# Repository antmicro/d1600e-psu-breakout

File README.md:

# Antmicro's open source D1600E PSU Breakout Board

Copyright (c) 2022-2023 [Antmicro](https://www.antmicro.com)

## Overview

This project contains open hardware design files for a Power Supply Unit (PSU) breakout board compatible with [Dell D1600E-S0 PSU](https://www.dell.com/en-us/work/shop/dell-power-supply-ac-1600-watt-psu-io/apd/450-ahuc/computer-chassis-components). 
The design files were prepared in KiCad.

### Project structure:

The main directory contains the KiCad design files, LICENSE and README.
The remaining files are stored in the following directories:

* ``img`` - contains graphics for this README
* ``doc`` - contains generated schematics and other documentation
* ``assets`` - contains visual assets for showcasing this design on [Open Hardware Portal](https://openhardware.antmicro.com/boards/d1600e-psu-breakout) and [Antmicro Designer](https://designer.antmicro.com/hardware/devices/d1600e-psu-breakout).

## Key features

* 5x power output channels providing 12V over 8-pin PCI Express type (Molex/39288080) sockets
* Up to 220W per single 12V power output channel
* Output current measurement implemented with [Ti/TMCS1100A2QDRQ1](https://www.ti.com/lit/ds/symlink/tmcs1100-q1.pdf) Hall sensors and 12-bit [Ti/ADS7828E](https://www.ti.com/lit/ds/symlink/ads7828.pdf) ADC accessible over I2C
* Power-cycling for each channel implemented with power MOSFETS driven from [Ti/TCA9534](https://www.ti.com/lit/ds/symlink/tca9534.pdf) GPIO expander accessible over I2C 
* I2C bus for current measurements and power cycling is opto-coupled with [FTDI/FT4232H-56Q](https://www.ftdichip.com/Support/Documents/DataSheets/ICs/DS_FT4232H.pdf) with USB exposed towards an external host
* Auxilary connector (Molex/39281103) exposing 5.0V,3.3V,12V for connecting external peripherals

## License

This project is published under the [Apache-2.0](LICENSE) license.

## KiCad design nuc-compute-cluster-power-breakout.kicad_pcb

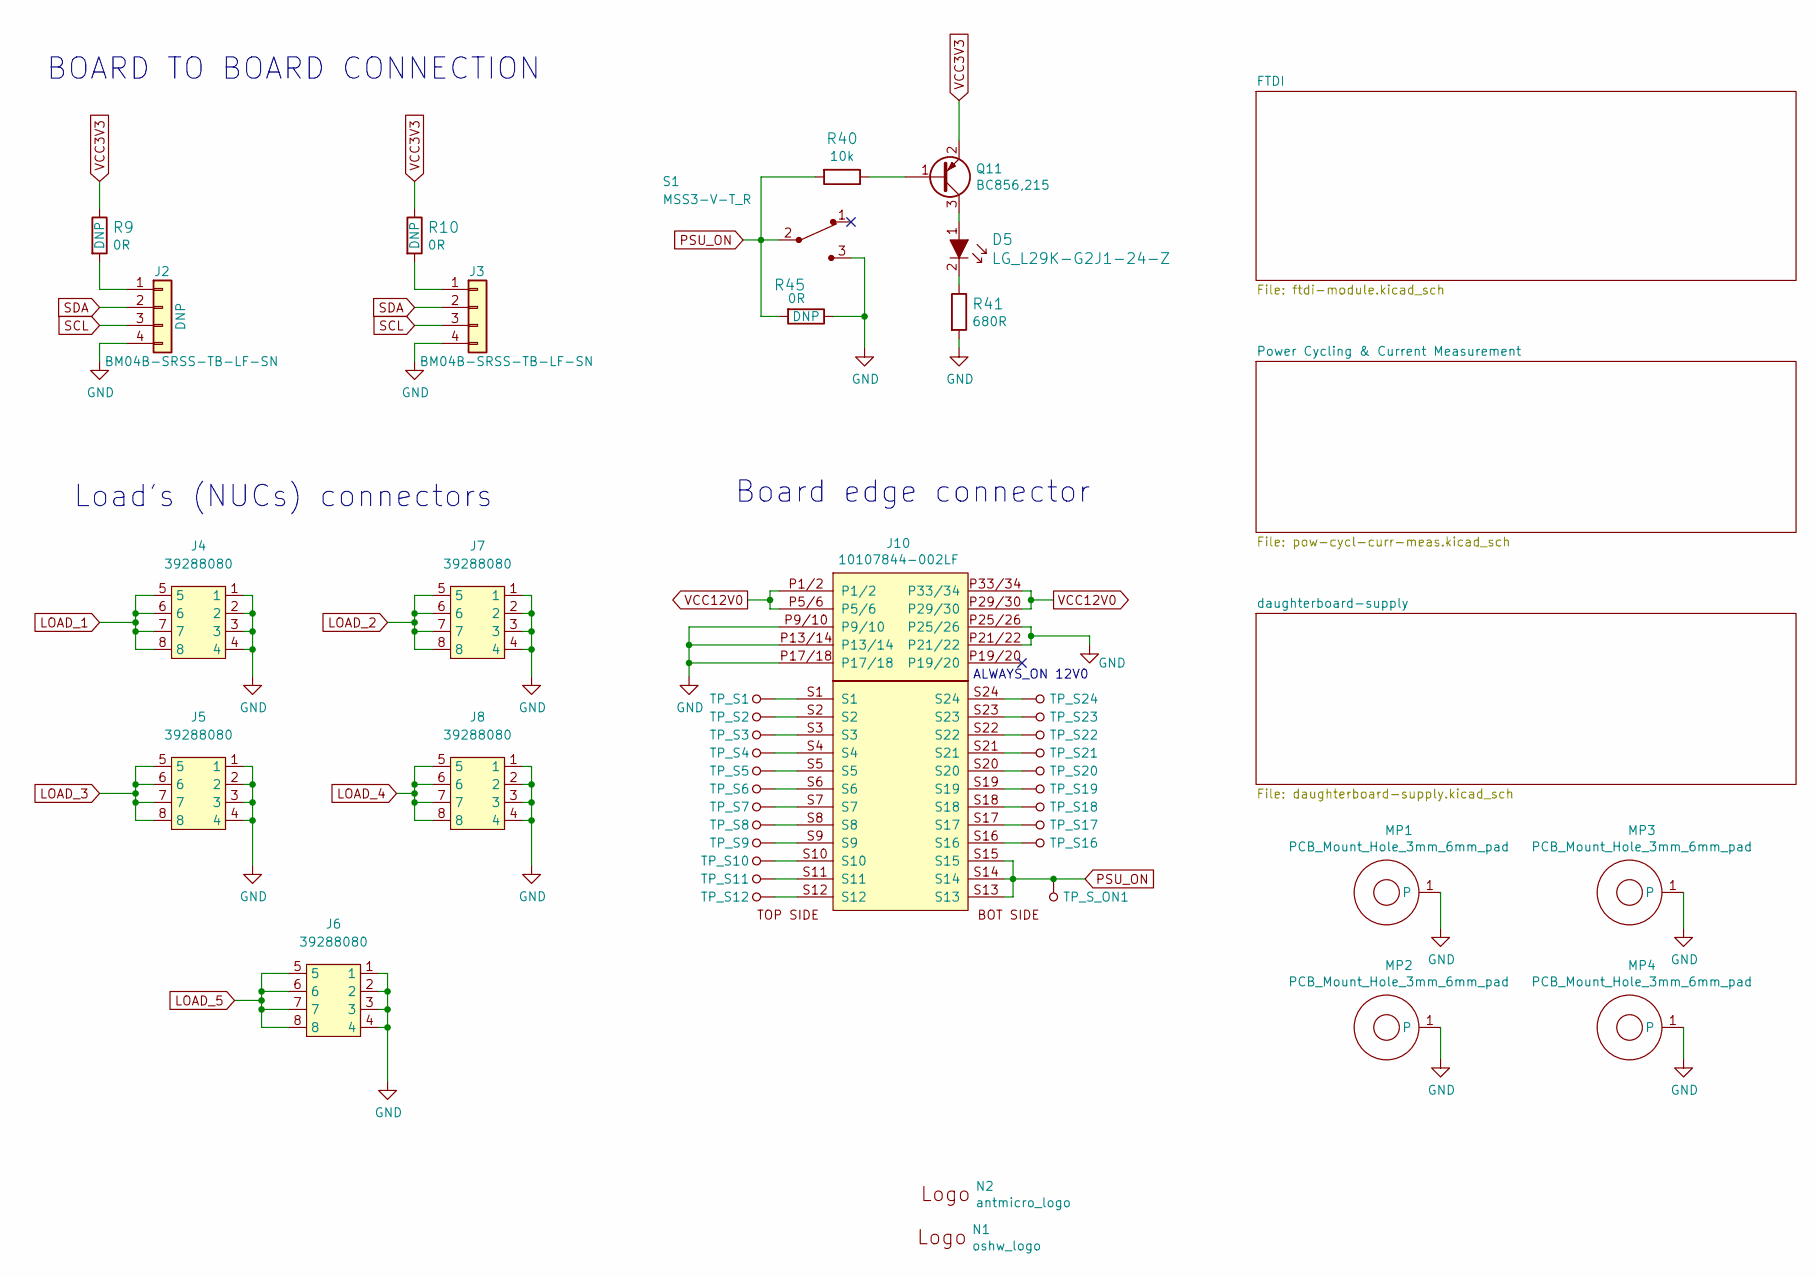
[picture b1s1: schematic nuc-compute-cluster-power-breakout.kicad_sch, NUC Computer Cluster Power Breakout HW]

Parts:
D5: LG_L29K-G2J1-24-Z; LED_0603; MPN LG L29K-G2J1-24-Z
J2, J3: BM04B-SRSS-TB-LF-SN; MPN BM04B-SRSS-TB(LF)(SN)
J4, J5, J6, J7, J8: 39288080; MOLEX_39288080; MPN 39288080
J10: 10107844-002LF; MPN 10107844-002LF
MP1, MP2, MP3, MP4: PCB_Mount_Hole_3mm_6mm_pad; mounting-hole-3.2mm
N1: oshw_logo; OSHW-Logo_7.5x8mm_Mask
N2: antmicro_logo; antmicro-logo_scaled_20mm_mask
Q11: BC856,215; SOT-23-3; MPN BC856,215
R9, R10, R45: R_0R_0402; 0402-res; MPN ERJ2GE0R00X
R40: R_10k_0402; 0402-res; MPN CRCW040210K0FKEDHP
R41: R_680R_0402; 0402-res; MPN 0402WGJ0681TCE
S1: MSS3-V-T_R; Switch_Slide_MSS3; MPN MSS3-V-T/R
TP_S1, TP_S2, TP_S3, TP_S4, TP_S5, TP_S6, TP_S7, TP_S8, TP_S9, TP_S10, TP_S11, TP_S12, TP_S16, TP_S17, TP_S18, TP_S19, TP_S20, TP_S21, TP_S22, TP_S23, TP_S24: TP_SMD1MM; Testpoint_smd_1mm
TP_S_ON1: TP_SMD1MM; Testpoint_smd_1mm

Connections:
GND: J2.4, J3.4, J4.1, J4.2, J4.3, J4.4, J5.1, J5.2, J5.3, J5.4, J6.1, J6.2, J6.3, J6.4, J7.1, J7.2, J7.3, J7.4, J8.1, J8.2, J8.3, J8.4, J10.P9/10, J10.P11/12, J10.P13/14, J10.P15/16, J10.P17/18, J10.P21/22, J10.P23/24, J10.P25/26, J10.P27/28, MP1.1, MP2.1, MP3.1, MP4.1, R41.2, R45.1, S1.3; also elsewhere on the board
LOAD_1: J4.5, J4.6, J4.7, J4.8; also elsewhere on the board
LOAD_2: J7.5, J7.6, J7.7, J7.8; also elsewhere on the board
LOAD_3: J5.5, J5.6, J5.7, J5.8; also elsewhere on the board
LOAD_4: J8.5, J8.6, J8.7, J8.8; also elsewhere on the board
LOAD_5: J6.5, J6.6, J6.7, J6.8; also elsewhere on the board
unnamed: D5.1, Q11.3
unnamed: D5.2, R41.1
unnamed: J2.1, R9.2
unnamed: J3.1, R10.2
unnamed: J10.S1, TP_S1.1
unnamed: J10.S2, TP_S2.1
unnamed: J10.S3, TP_S3.1
unnamed: J10.S4, TP_S4.1
unnamed: J10.S5, TP_S5.1
unnamed: J10.S6, TP_S6.1
unnamed: J10.S7, TP_S7.1
unnamed: J10.S8, TP_S8.1
unnamed: J10.S9, TP_S9.1
unnamed: J10.S10, TP_S10.1
unnamed: J10.S11, TP_S11.1
unnamed: J10.S12, TP_S12.1
unnamed: J10.S16, TP_S16.1
unnamed: J10.S17, TP_S17.1
unnamed: J10.S18, TP_S18.1
unnamed: J10.S19, TP_S19.1
unnamed: J10.S20, TP_S20.1
unnamed: J10.S21, TP_S21.1
unnamed: J10.S22, TP_S22.1
unnamed: J10.S23, TP_S23.1
unnamed: J10.S24, TP_S24.1
unnamed: Q11.1, R40.1
PSU_ON: J10.S13, J10.S14, J10.S15, R40.2, R45.2, S1.2, TP_S_ON1.1
SCL: J2.3, J3.3; also elsewhere on the board
SDA: J2.2, J3.2; also elsewhere on the board
VCC3V3: Q11.2, R9.1, R10.1; also elsewhere on the board
VCC12V0: J10.P1/2, J10.P3/4, J10.P5/6, J10.P7/8, J10.P29/30, J10.P31/32, J10.P33/34, J10.P35/36; also elsewhere on the board

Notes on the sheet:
Board edge connector
ALWAYS_ON 12V0
BOARD TO BOARD CONNECTION
Load's (NUCs) connectors

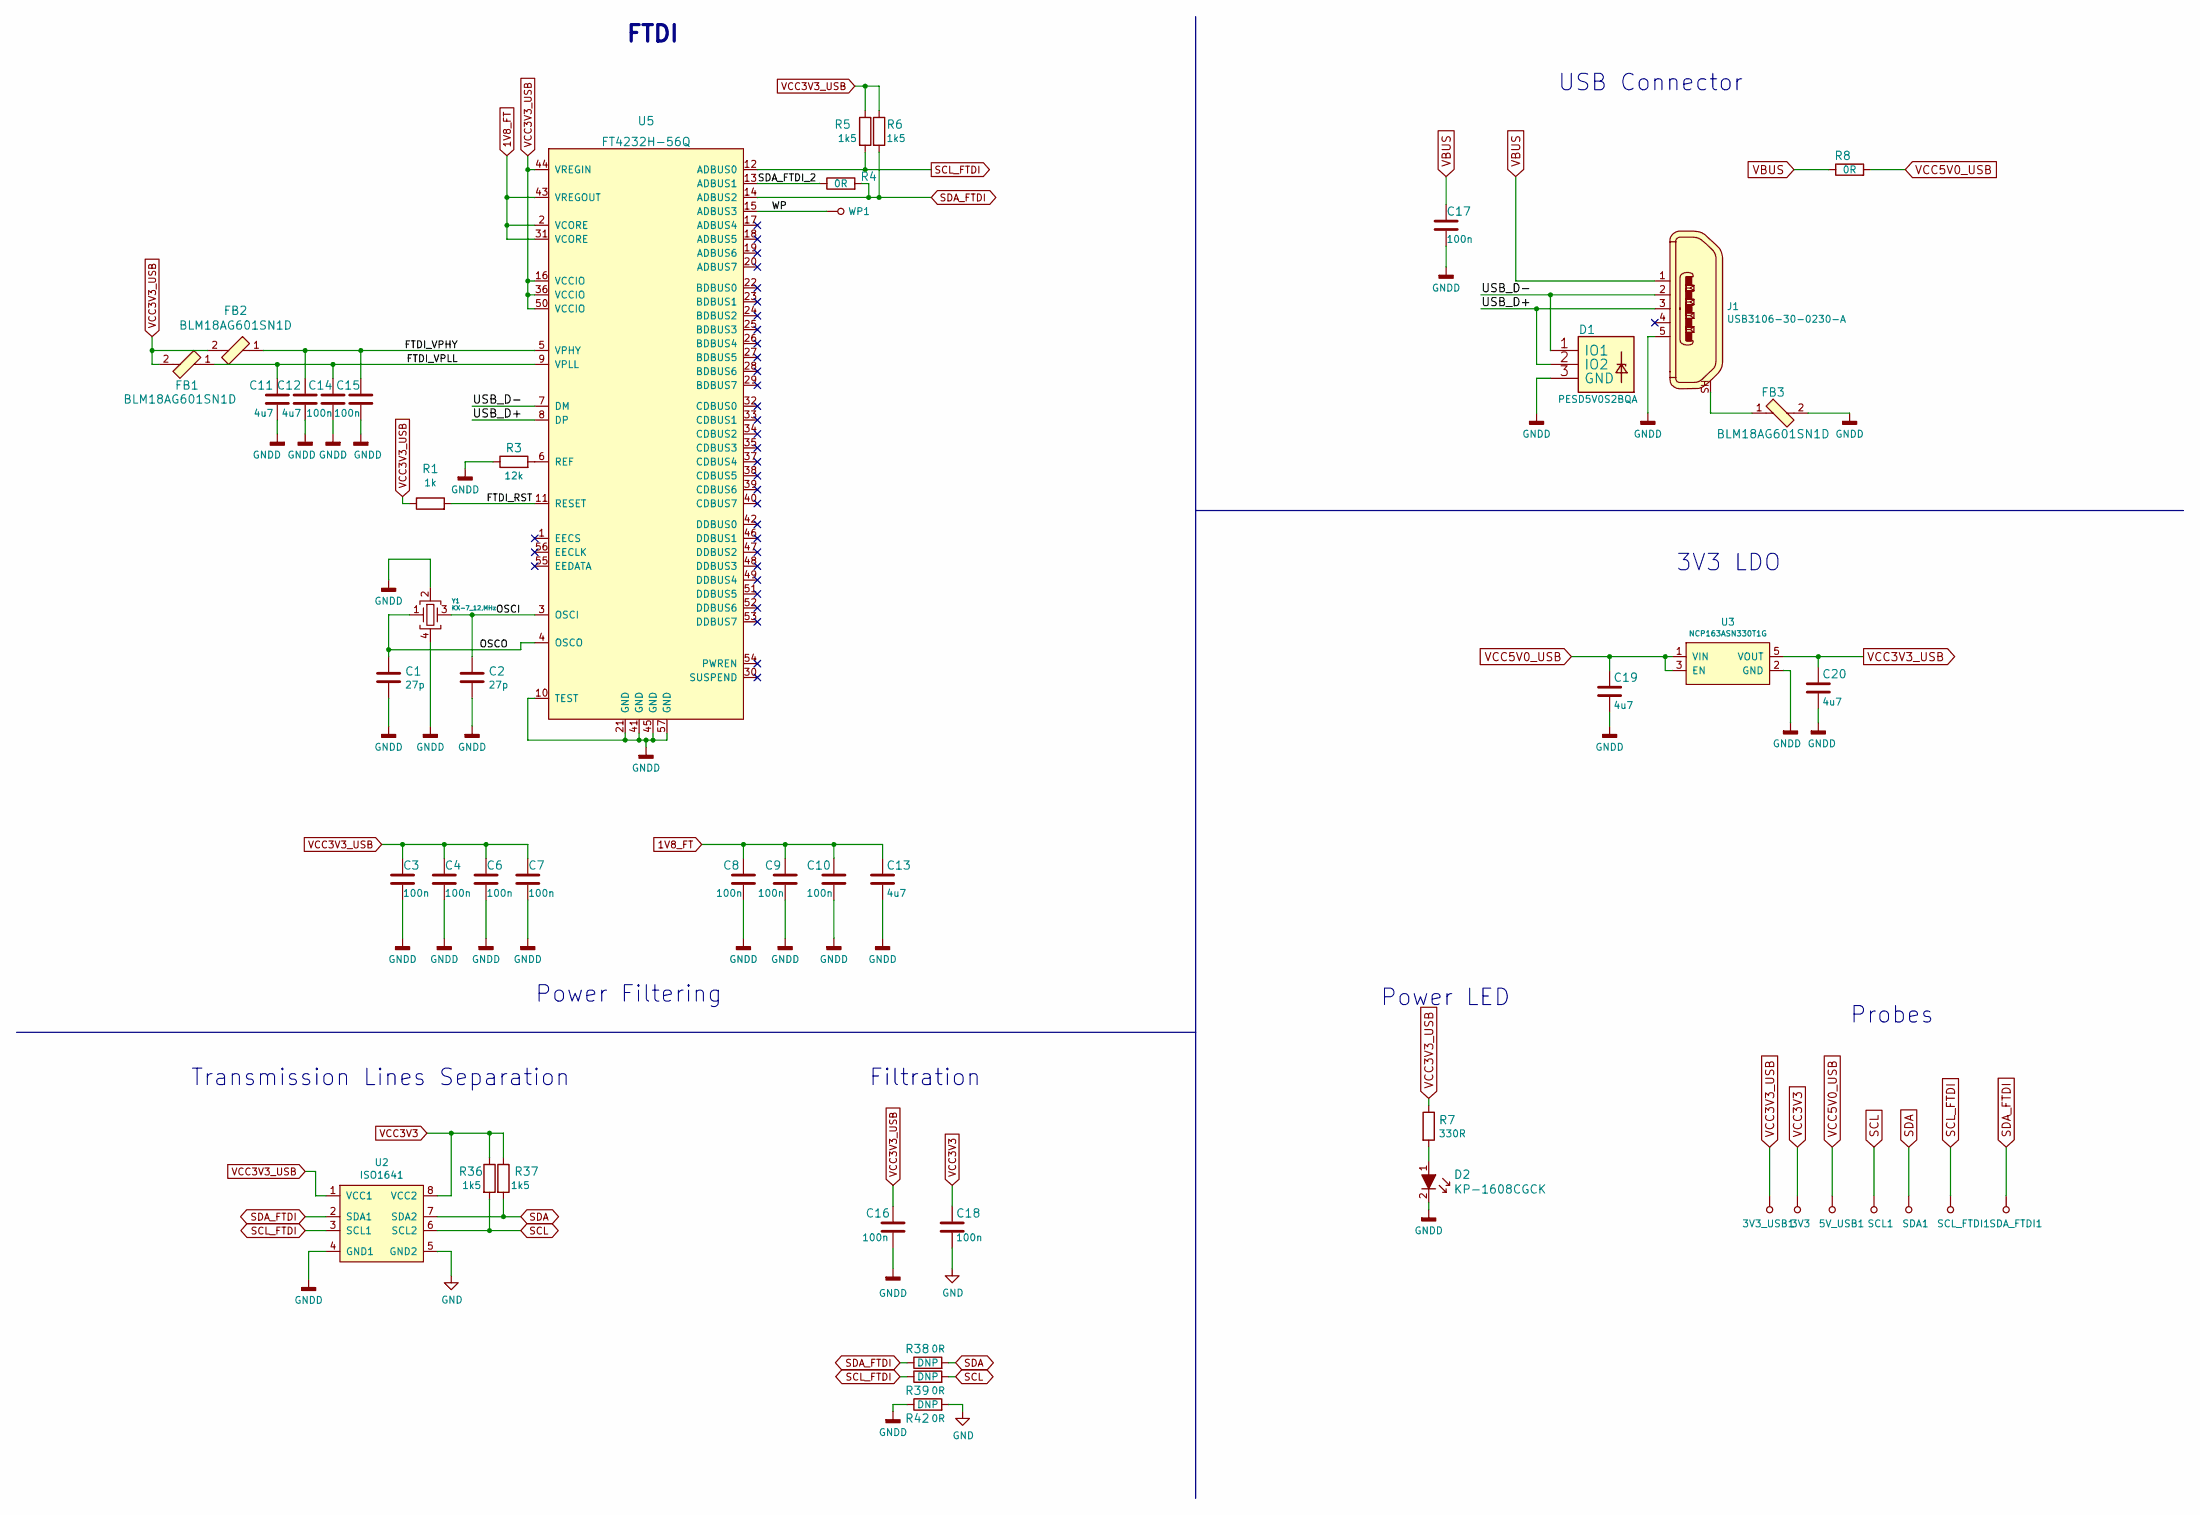
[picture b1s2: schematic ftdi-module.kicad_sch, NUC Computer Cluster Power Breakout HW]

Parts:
3V3, 3V3_USB1, 5V_USB1: TP_SMD1MM; Testpoint_smd_1mm
C1, C2: C_27p_0402; 0402-cap; MPN 0402N270J500CT
C3, C4, C6, C7, C8, C9, C10, C14, C15, C16, C17, C18: C_100n_0402; 0402-cap; MPN GRM155R61H104KE14D
C11, C12, C13, C19, C20: C_4u7_0402; 0402-cap; MPN GRM155R61A475MEAAD
D1: PESD5V0S2BQA; TPD2E009DRTR; MPN PESD5V0S2BQA
D2: KP-1608CGCK; LED_0603; MPN KP-1608CGCK
FB1, FB2, FB3: BLM18AG601SN1D; 0603; MPN BLM18AG601SN1D
J1: USB3106-30-0230-A; usb3106-30-0230; MPN USB3106-30-0230-A
R1: R_1k_0402; 0402-res; MPN CR0402-FX-1001GLF
R3: R_12k_0402; 0402-res; MPN CRCW040212K0FKEDHP
R4, R8, R38, R39, R42: R_0R_0603; 0603-res; MPN CR0603-J/-000ELF
R5, R6, R36, R37: R_1k5_0402; 0402-res; MPN MP000515
R7: R_330R_0402; 0402-res; MPN MCMR04X3300FTL
SCL1: TP_SMD1MM; Testpoint_smd_1mm
SCL_FTDI1: TP_SMD1MM; Testpoint_smd_1mm
SDA1: TP_SMD1MM; Testpoint_smd_1mm
SDA_FTDI1: TP_SMD1MM; Testpoint_smd_1mm
U2: ISO1641; SOIC-8_W3.9mm; MPN ISO1641BDR
U3: NCP163ASN330T1G; SOT-23-5; MPN NCP163ASN330T1G
U5: FT4232H-56Q; QFN-56-1EP_8x8mm_P0.5mm_EP5.5.9x5.9mm; MPN FT4232H-56Q-REEL
WP1: TP_SMD1MM; Testpoint_smd_1mm
Y1: KX-7_12,MHz; KX-7; MPN KX-7_SMD_CRYSTAL_12,0 MHZ

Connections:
1V8_FT: C8.1, C9.1, C10.1, C13.1, U5.2 (VCORE), U5.31 (VCORE), U5.43 (VREGOUT)
/FTDI/FTDI_RST: R1.2, U5.11 (RESET)
/FTDI/FTDI_VPHY: C12.1, C15.1, FB2.1, U5.5 (VPHY)
/FTDI/FTDI_VPLL: C11.1, C14.1, FB1.1, U5.9 (VPLL)
/FTDI/OSCI: C2.1, U5.3 (OSCI), Y1.3
/FTDI/OSCO: C1.1, U5.4 (OSCO), Y1.1
/FTDI/SDA_FTDI_2: R4.1, U5.13 (ADBUS1)
/FTDI/USB_D+: D1.2 (IO2), J1.3, U5.8 (DP)
/FTDI/USB_D-: D1.1 (IO1), J1.2, U5.7 (DM)
/FTDI/WP: U5.15 (ADBUS3), WP1.1
GND: C18.2, R42.2, U2.5 (GND2); also elsewhere on the board
GNDD: C1.2, C2.2, C3.2, C4.2, C6.2, C7.2, C8.2, C9.2, C10.2, C11.2, C12.2, C13.2, C14.2, C15.2, C16.2, C17.2, C19.2, C20.2, D1.3 (GND), D2.2, FB3.2, J1.5, R3.1, R42.1, U2.4 (GND1), U3.2 (GND), U5.10 (TEST), U5.21 (GND), U5.41 (GND), U5.45 (GND), U5.57 (GND), Y1.2, Y1.4
unnamed: D2.1, R7.2
unnamed: FB3.1, J1.SH
unnamed: R3.2, U5.6 (REF)
SCL: R36.2, R39.2, SCL1.1, U2.6 (SCL2); also elsewhere on the board
SCL_FTDI: R5.2, R39.1, SCL_FTDI1.1, U2.3 (SCL1), U5.12 (ADBUS0)
SDA: R37.2, R38.2, SDA1.1, U2.7 (SDA2); also elsewhere on the board
SDA_FTDI: R4.2, R6.2, R38.1, SDA_FTDI1.1, U2.2 (SDA1), U5.14 (ADBUS2)
VBUS: C17.1, J1.1, R8.1
VCC3V3: 3V3.1, C18.1, R36.1, R37.1, U2.8 (VCC2); also elsewhere on the board
VCC3V3_USB: 3V3_USB1.1, C3.1, C4.1, C6.1, C7.1, C16.1, C20.1, FB1.2, FB2.2, R1.1, R5.1, R6.1, R7.1, U2.1 (VCC1), U3.5 (VOUT), U5.16 (VCCIO), U5.36 (VCCIO), U5.44 (VREGIN), U5.50 (VCCIO)
VCC5V0_USB: 5V_USB1.1, C19.1, R8.2, U3.1 (VIN), U3.3 (EN)

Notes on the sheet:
FTDI
Power Filtering
USB Connector
Transmission Lines Separation
Probes
Filtration
Power LED
3V3 LDO

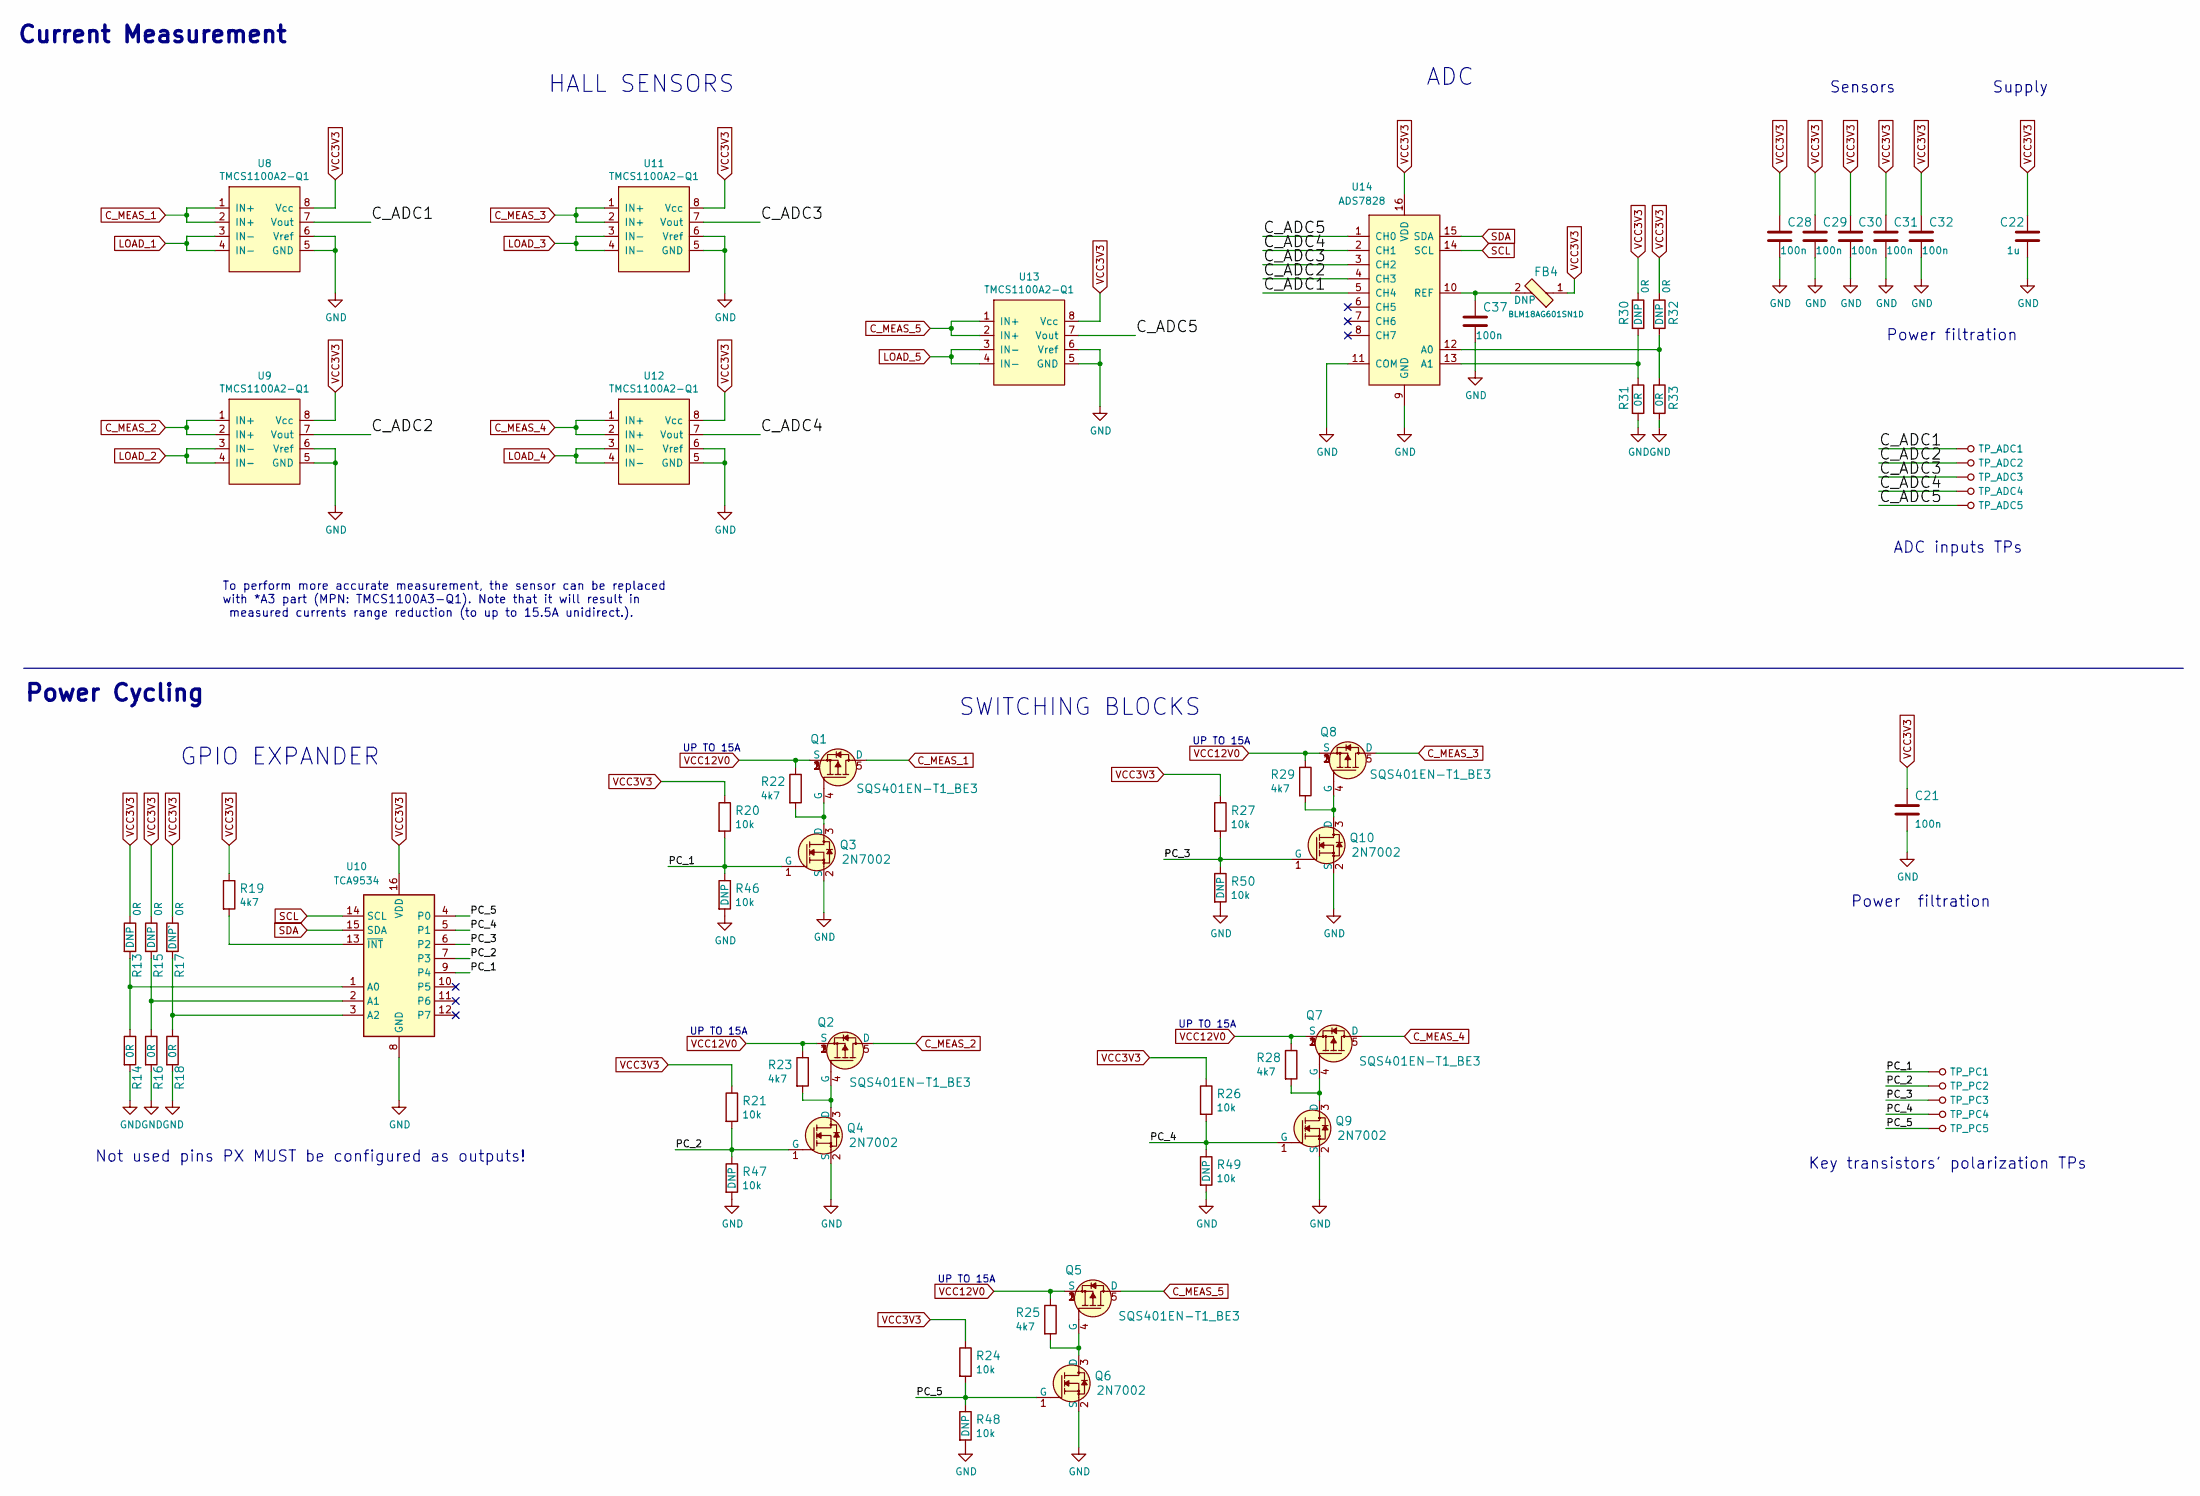
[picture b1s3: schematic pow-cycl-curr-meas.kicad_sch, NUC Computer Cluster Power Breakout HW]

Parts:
C21, C28, C29, C30, C31, C32, C37: C_100n_0402; 0402-cap; MPN GRM155R61H104KE14D
C22: C_1u_0402; 0402-cap; MPN C1005X6S1A105K050BC
FB4: BLM18AG601SN1D; 0603; MPN BLM18AG601SN1D
Q1, Q2, Q5, Q7, Q8: SQS401EN-T1_BE3; Vishay_PowerPAK_1212-8_Single; MPN SQS401EN-T1_BE3
Q3, Q4, Q6, Q9, Q10: 2N7002; SOT-23-3; MPN 2N7002
R13, R14, R15, R16, R17, R18, R30, R31, R32, R33: R_0R_0402; 0402-res; MPN ERJ2GE0R00X
R19, R22, R23, R25, R28, R29: R_4k7_0402; 0402-res; MPN MCS04020C4701FE000
R20, R21, R24, R26, R27, R46, R47, R48, R49, R50: R_10k_0402; 0402-res; MPN CRCW040210K0FKEDHP
TP_ADC1, TP_ADC2, TP_ADC3, TP_ADC4, TP_ADC5: TP_SMD1MM; Testpoint_smd_1mm
TP_PC1, TP_PC2, TP_PC3, TP_PC4, TP_PC5: TP_SMD1MM; Testpoint_smd_1mm
U8, U9, U11, U12, U13: TMCS1100A2-Q1; SOIC-8_W3.9mm; MPN TMCS1100A2QDRQ1
U10: TCA9534; TSSOP-16; MPN TCA9534ADWR
U14: ADS7828; TSSOP-16_4.4x5mm_P0.65mm; MPN ADS7828E/250

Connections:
/Power Cycling & Current Measurement/C_ADC1: TP_ADC1.1, U8.7 (Vout), U14.5 (CH4)
/Power Cycling & Current Measurement/C_ADC2: TP_ADC2.1, U9.7 (Vout), U14.4 (CH3)
/Power Cycling & Current Measurement/C_ADC3: TP_ADC3.1, U11.7 (Vout), U14.3 (CH2)
/Power Cycling & Current Measurement/C_ADC4: TP_ADC4.1, U12.7 (Vout), U14.2 (CH1)
/Power Cycling & Current Measurement/C_ADC5: TP_ADC5.1, U13.7 (Vout), U14.1 (CH0)
/Power Cycling & Current Measurement/PC_1: Q3.1 (G), R20.2, R46.1, TP_PC1.1, U10.9 (P4)
/Power Cycling & Current Measurement/PC_2: Q4.1 (G), R21.2, R47.1, TP_PC2.1, U10.7 (P3)
/Power Cycling & Current Measurement/PC_3: Q10.1 (G), R27.2, R50.1, TP_PC3.1, U10.6 (P2)
/Power Cycling & Current Measurement/PC_4: Q9.1 (G), R26.2, R49.1, TP_PC4.1, U10.5 (P1)
/Power Cycling & Current Measurement/PC_5: Q6.1 (G), R24.2, R48.1, TP_PC5.1, U10.4 (P0)
C_MEAS_1: Q1.5 (D), U8.1 (IN+), U8.2 (IN+)
C_MEAS_2: Q2.5 (D), U9.1 (IN+), U9.2 (IN+)
C_MEAS_3: Q8.5 (D), U11.1 (IN+), U11.2 (IN+)
C_MEAS_4: Q7.5 (D), U12.1 (IN+), U12.2 (IN+)
C_MEAS_5: Q5.5 (D), U13.1 (IN+), U13.2 (IN+)
GND: C21.2, C22.2, C28.2, C29.2, C30.2, C31.2, C32.2, C37.2, Q3.2 (S), Q4.2 (S), Q6.2 (S), Q9.2 (S), Q10.2 (S), R14.2, R16.2, R18.2, R31.2, R33.2, R46.2, R47.2, R48.2, R49.2, R50.2, U8.5 (GND), U8.6 (Vref), U9.5 (GND), U9.6 (Vref), U10.8 (GND), U11.5 (GND), U11.6 (Vref), U12.5 (GND), U12.6 (Vref), U13.5 (GND), U13.6 (Vref), U14.9 (GND), U14.11 (COM); also elsewhere on the board
LOAD_1: U8.3 (IN-), U8.4 (IN-); also elsewhere on the board
LOAD_2: U9.3 (IN-), U9.4 (IN-); also elsewhere on the board
LOAD_3: U11.3 (IN-), U11.4 (IN-); also elsewhere on the board
LOAD_4: U12.3 (IN-), U12.4 (IN-); also elsewhere on the board
LOAD_5: U13.3 (IN-), U13.4 (IN-); also elsewhere on the board
unnamed: C37.1, FB4.2, U14.10 (REF)
unnamed: Q1.4 (G), Q3.3 (D), R22.2
unnamed: Q2.4 (G), Q4.3 (D), R23.2
unnamed: Q5.4 (G), Q6.3 (D), R25.2
unnamed: Q7.4 (G), Q9.3 (D), R28.2
unnamed: Q8.4 (G), Q10.3 (D), R29.2
unnamed: R13.2, R14.1, U10.1 (A0)
unnamed: R15.2, R16.1, U10.2 (A1)
unnamed: R17.2, R18.1, U10.3 (A2)
unnamed: R19.2, U10.13 (~INT)
unnamed: R30.2, R31.1, U14.13 (A1)
unnamed: R32.2, R33.1, U14.12 (A0)
SCL: U10.14 (SCL), U14.14 (SCL); also elsewhere on the board
SDA: U10.15 (SDA), U14.15 (SDA); also elsewhere on the board
VCC3V3: C21.1, C22.1, C28.1, C29.1, C30.1, C31.1, C32.1, FB4.1, R13.1, R15.1, R17.1, R19.1, R20.1, R21.1, R24.1, R26.1, R27.1, R30.1, R32.1, U8.8 (Vcc), U9.8 (Vcc), U10.16 (VDD), U11.8 (Vcc), U12.8 (Vcc), U13.8 (Vcc), U14.16 (VDD); also elsewhere on the board
VCC12V0: Q1.1 (S), Q1.2 (S), Q1.3 (S), Q2.1 (S), Q2.2 (S), Q2.3 (S), Q5.1 (S), Q5.2 (S), Q5.3 (S), Q7.1 (S), Q7.2 (S), Q7.3 (S), Q8.1 (S), Q8.2 (S), Q8.3 (S), R22.1, R23.1, R25.1, R28.1, R29.1; also elsewhere on the board

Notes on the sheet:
Not used pins PX MUST be configured as outputs!
Current Measurement
ADC inputs TPs
SWITCHING BLOCKS
Key transistors' polarization TPs
ADC
UP TO 15A
GPIO EXPANDER
To perform more accurate measurement, the sensor can be replaced with *A3 part (MPN: TMCS1100A3-Q1). Note that it will result in measured currents range reduction (to up to 15.5A unidirect.).
HALL SENSORS
Power filtration
Sensors
Supply
Power filtration
Power Cycling

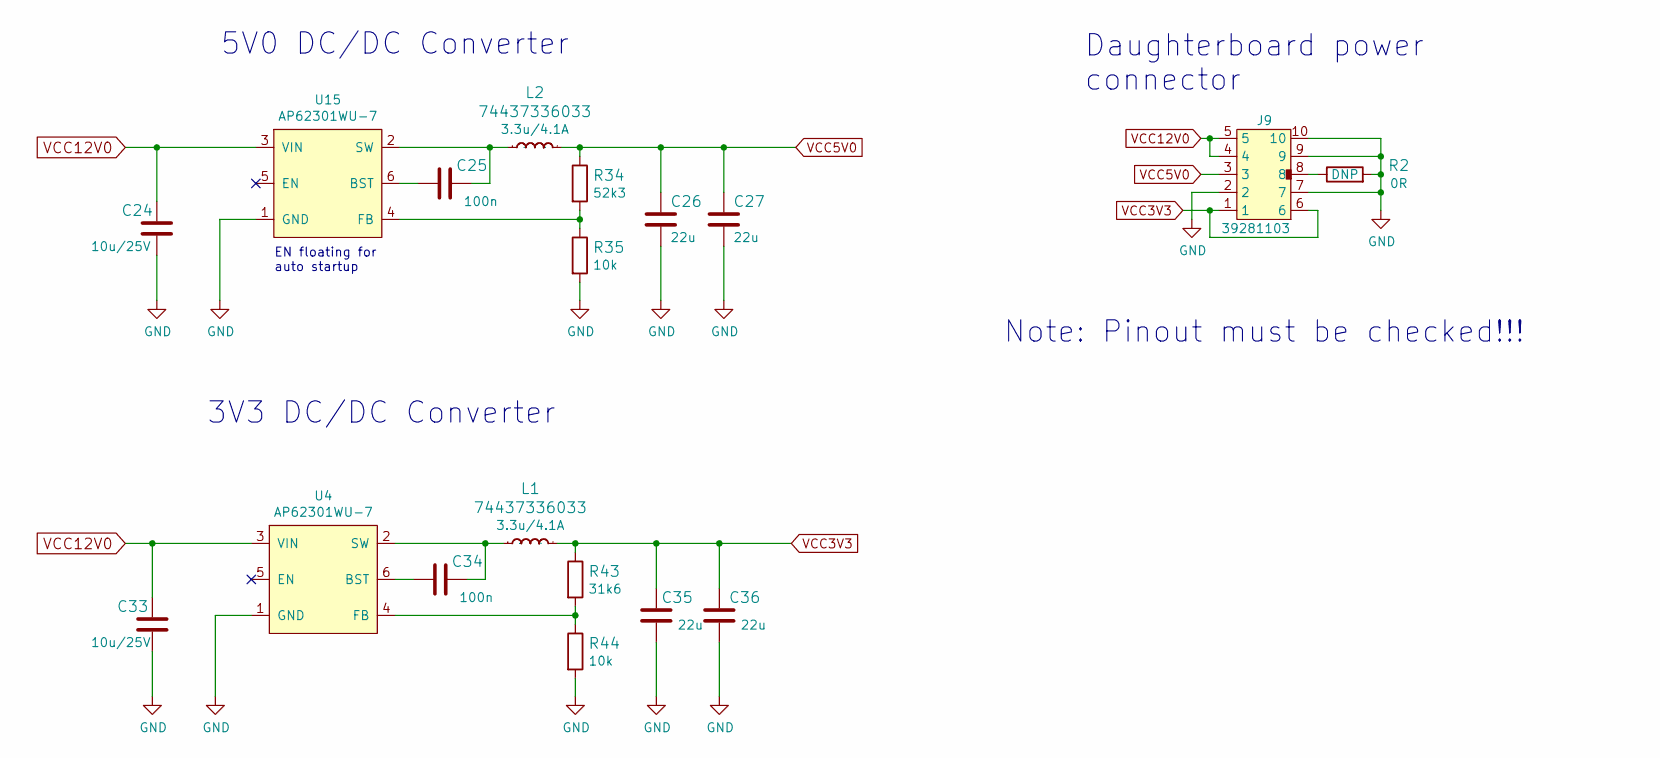
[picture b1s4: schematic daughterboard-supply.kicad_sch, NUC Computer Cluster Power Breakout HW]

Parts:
C24, C33: C_10u_16V_0603; 0603-cap; MPN C1608X5R1E106M080AC
C25, C34: C_100n_0402; 0402-cap; MPN GRM155R61H104KE14D
C26, C27, C35, C36: C_22u_0603; 0603-cap; MPN GRM188R60J226MEA0D
J9: 39281103; MOLEX_39281103; MPN 39281103
L1, L2: 74437336033; WE_74437336033; MPN 74437336033
R2: R_0R_0402; 0402-res; MPN ERJ2GE0R00X
R34: R_52k3_0402; 0402-res; MPN ERJ-2RKF5232X
R35, R44: R_10k_0402; 0402-res; MPN CRCW040210K0FKEDHP
R43: R_31k6_0402; 0402-res; MPN CRCW040231K6FKEDC
U4, U15: AP62301WU-7; TSOT23-6; MPN AP62301WU-7

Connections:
GND: C24.2, C26.2, C27.2, C33.2, C35.2, C36.2, J9.2, J9.7, J9.9, J9.10, R2.2, R35.2, R44.2, U4.1 (GND), U15.1 (GND); also elsewhere on the board
unnamed: C25.1, L2.1, U15.2 (SW)
unnamed: C25.2, U15.6 (BST)
unnamed: C34.1, L1.1, U4.2 (SW)
unnamed: C34.2, U4.6 (BST)
unnamed: J9.8, R2.1
unnamed: R34.2, R35.1, U15.4 (FB)
unnamed: R43.2, R44.1, U4.4 (FB)
VCC3V3: C35.1, C36.1, J9.1, J9.6, L1.2, R43.1; also elsewhere on the board
VCC5V0: C26.1, C27.1, J9.3, L2.2, R34.1
VCC12V0: C24.1, C33.1, J9.4, J9.5, U4.3 (VIN), U15.3 (VIN); also elsewhere on the board

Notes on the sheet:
5V0 DC/DC Converter
Daughterboard power connector
3V3 DC/DC Converter
EN floating for auto startup
Note: Pinout must be checked!!!

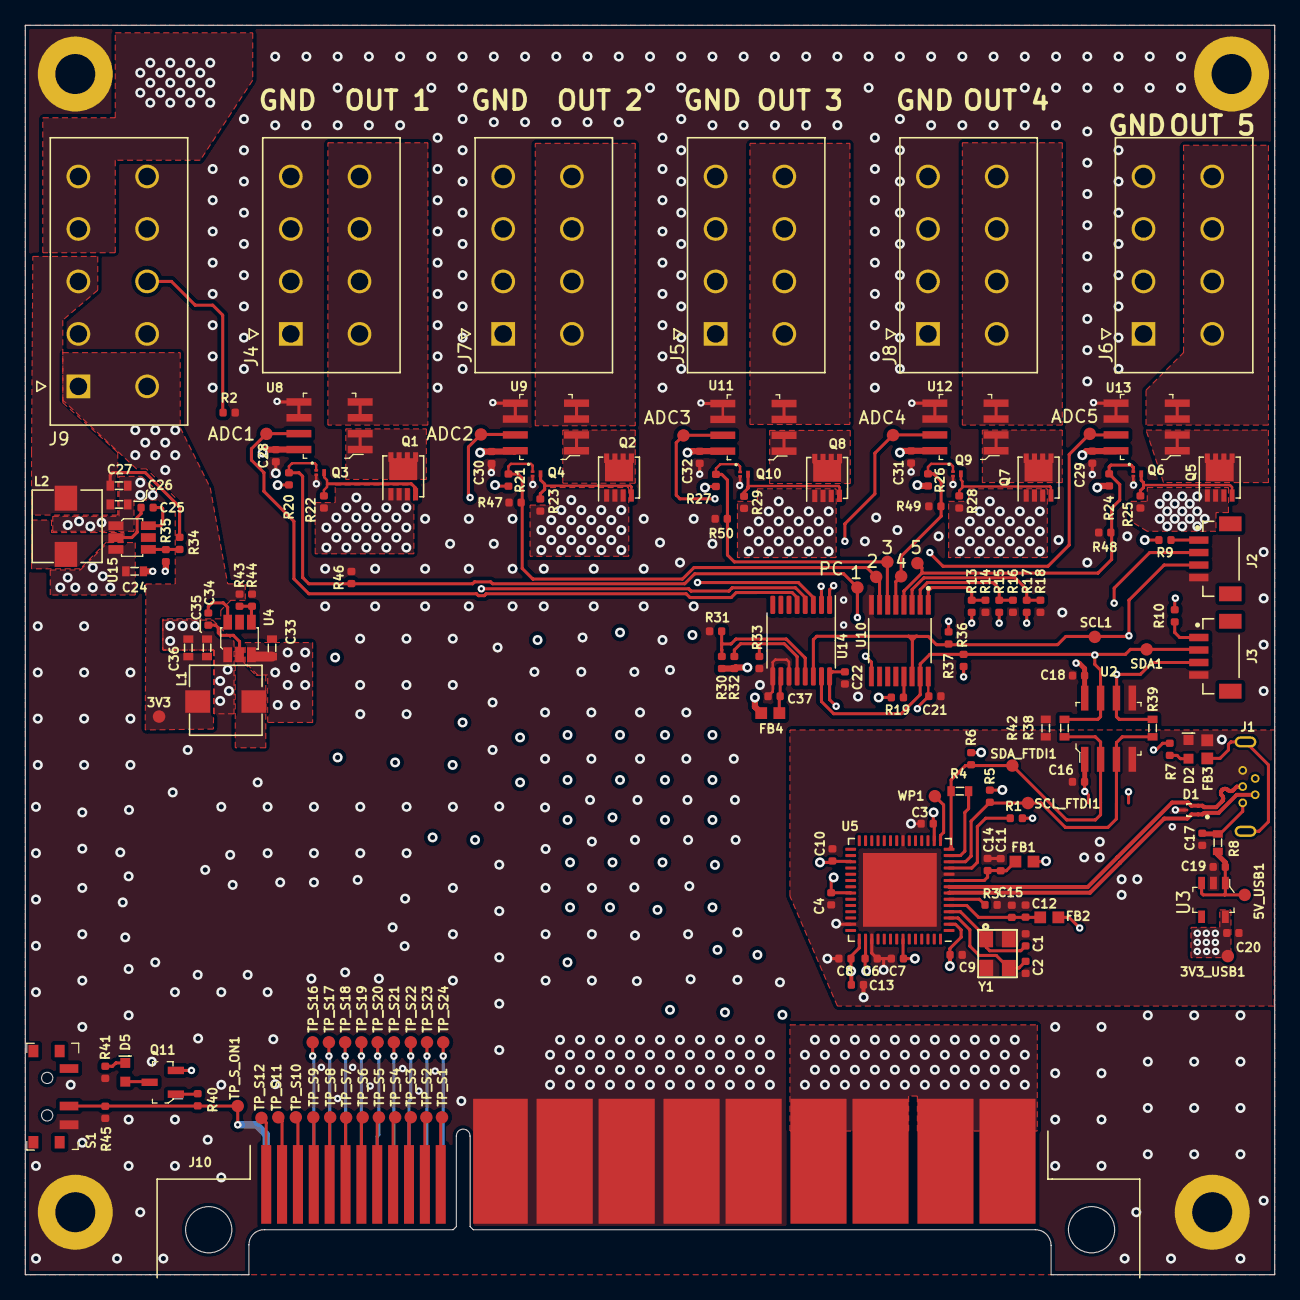
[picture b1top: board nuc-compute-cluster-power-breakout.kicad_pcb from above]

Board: 4 copper layers, 100.0 x 100.0 mm, 173 parts (0 on the bottom side), 91 nets.

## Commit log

2022-03-03 add README
2022-03-03 Initial commit - KiCAD project
2022-03-03 FTDI schematic update
2022-03-04 FTDI module complete
2022-03-07 Small improvements. Power cycling module sheet
2022-03-08 Power cycling module improvement
2022-03-11 Power cycling module update
2022-03-11 Logic Shifter Module. Current Meas. implementation
2022-03-14 Current Module upgrade. Logic unification.
2022-03-15 Added connection between breakout boards
2022-03-17 Schematic improvements according to review's comments
2022-03-18 Remove backup of ftdi-module
2022-03-18 Change schematic sheet's name
2022-03-18 Add logos
2022-03-18 Remove power diodes
2022-03-18 loclib
2022-09-29 Power planes alignment
2022-09-29 Add remarks to the PCB file
2022-09-29 Labels unification
2022-09-29 small improvement
2022-09-29 PCB creation. Components gathered in functional groups
2022-09-29 First revision of PCB finished
2022-09-29 Routing and power planes
2022-09-29 FTDI layout redesign
2022-09-29 Initial routing. Small schematics improvements
2022-09-29 Added power switch. PCB update.
2022-09-29 Initial component placement done
2022-09-29 Added power distribution connectors
2022-09-29 Added power connectors
2022-09-29 Added stitching and mounting holes
2022-09-29 Improvements after review
2022-09-29 Loclib update
2022-09-29 Schematic complete
2022-09-29 Add remarks on the schematic sheets
2022-09-29 PCB update
2022-09-29 Added switch for daughterboard's supply
2022-09-29 Replaced +3V3 with GND plane
2022-09-29 Added PSU power on switch
2022-09-29 Finished layout and fixed silkscreen
2022-09-29 Replaced FTDI chip with FT4232H-56Q on the schematic
2022-09-29 Schematic visual update
2022-09-29 Performed loclib
2022-09-29 Loclib performed
2022-09-29 Transistors orientation fix
2022-09-29 Switching transistor bug fix
2022-09-29 Fixed swapped I2C lines Corrected silkscreen layer Rearranged EdgeConn test points
2022-09-29 Eliminated DRC errors
2022-09-29 NUC's connector moved. Mounting holes repositioning
2022-09-29 Edge connector footprint update
2022-09-29 Label output channel names
2022-09-29 Misspell fix
2022-09-29 Changed power connectors
2022-09-29 project cleanup
2022-09-29 Unify the font
2022-09-29 Initial galvanic isolation added to layout
2022-09-29 Resolve annular ring DRC issues
2022-09-29 Add remarks to the schematic
2022-09-29 Added board cut-out. Logos replacement
2022-09-29 Add R45 to implement ALWAYS ON feature
2022-09-29 Update project to Kicad 6
2022-09-29 Added mising GND to schematic
2022-09-29 Update USB port footprint
2022-09-29 Layout of power connectors
2022-09-29 Galvanic isolation implementation
2022-09-29 Added LICENSE file.
2022-09-29 Added 3D vizualization files
2022-09-29 Revision bump to 1.3.0
2022-09-29 Added vizualization
2022-09-29 Fixed FTDI sheet
2022-09-29 Remove soldermask from Molex connectors, Increased pad sizes for Molex connectors
2022-09-29 Typo fix
2022-09-29 Adjust the power plane distribution
2022-09-29 Change the board name
2022-09-29 Revision update
2022-09-29 Complete galvanic isolated layout
2022-09-29 Patches after 2nd revision
2022-09-29 Added support for default off and changed converter cap voltage rating
2022-09-29 Introduction structure redesign
2022-09-29 README update
2022-09-29 Add photo, unify the size of schematic sheets
2022-09-29 Reverted accidental DRC rule change
2022-09-29 Added LED indicators
2022-09-29 Prototyping EC E1438847
2022-09-29 Replaced transistors with larger package
2022-09-29 Finished replacing FTDI chip on the PCB
2022-09-29 Added LED indicators for all voltage rails
2022-09-29 Bumped rev to 1.3.1
2022-10-19 Remove redundant file
2022-10-19 README: Add part numbers for relevant ICs
2022-10-19 README: minor fix
2022-10-19 Notes added by 'git notes add'
2022-12-12 Modified power planes to improve thermals of Q1-Q5 transistors #39747
2022-12-13 Replaced usb micro to USB C
2022-12-13 Added protection for I2C, fix resistor value for USB C, Fixed J9 reversed polarity, minor width fix to 3v3 line
2022-12-14 Solved all DRC warnings and errors
2022-12-15 Aded molex connectors for PCI-e risers and pul up down option for 5V info rail from coordinator
2022-12-16 Added some changes after 1st review
2022-12-21 Added all changes proposed in first review of the board
2022-12-22 Fixed USB tracks,VBUS&GNDD, DRC errors and warning, added protection zener diodes
2022-12-22 Added commit number to silkcreen, increased clearence on bottom layer near THT components
2022-12-22 Changed revision version and date on board and schematic
2023-02-06 Removed obsolete library from lib-table
2023-02-06 Added blendcfg
2023-02-06 Prepared voltage measurement schematic
2023-02-07 Removed obsolete library from sym-lib-table
2023-02-07 Finished voltage measurement schematics
2023-02-07 Implemented voltage measurement on PCB
2023-02-07 Exchanged resistor in divider for voltage measurement
2023-02-07 Bumped revision to 1.4.1
2023-02-08 Fixed IO expander MPN
2023-02-22 R34,R35,R43,R44 on daughterboard updated
2023-02-23 updated R34, R35, R43, R44
2023-03-31 README: minor fixes, add OSP badge
2023-08-02 Updated blendcfg
2023-08-02 Placed new blendcfg.yaml
2023-10-18 #50436 Add FTDI led control, bump revision to 1.4.2
2023-10-18 #50436 Set U2 as DNP, add assembly variant table, bump to 1.4.3
2024-10-02 [#63472] Add OHP assets
2024-10-09 [#66930] Replaced photos with new ones
